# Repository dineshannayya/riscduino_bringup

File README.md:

# mpw_bringup
Host all the MPW Bring-up related Enviornment

Update

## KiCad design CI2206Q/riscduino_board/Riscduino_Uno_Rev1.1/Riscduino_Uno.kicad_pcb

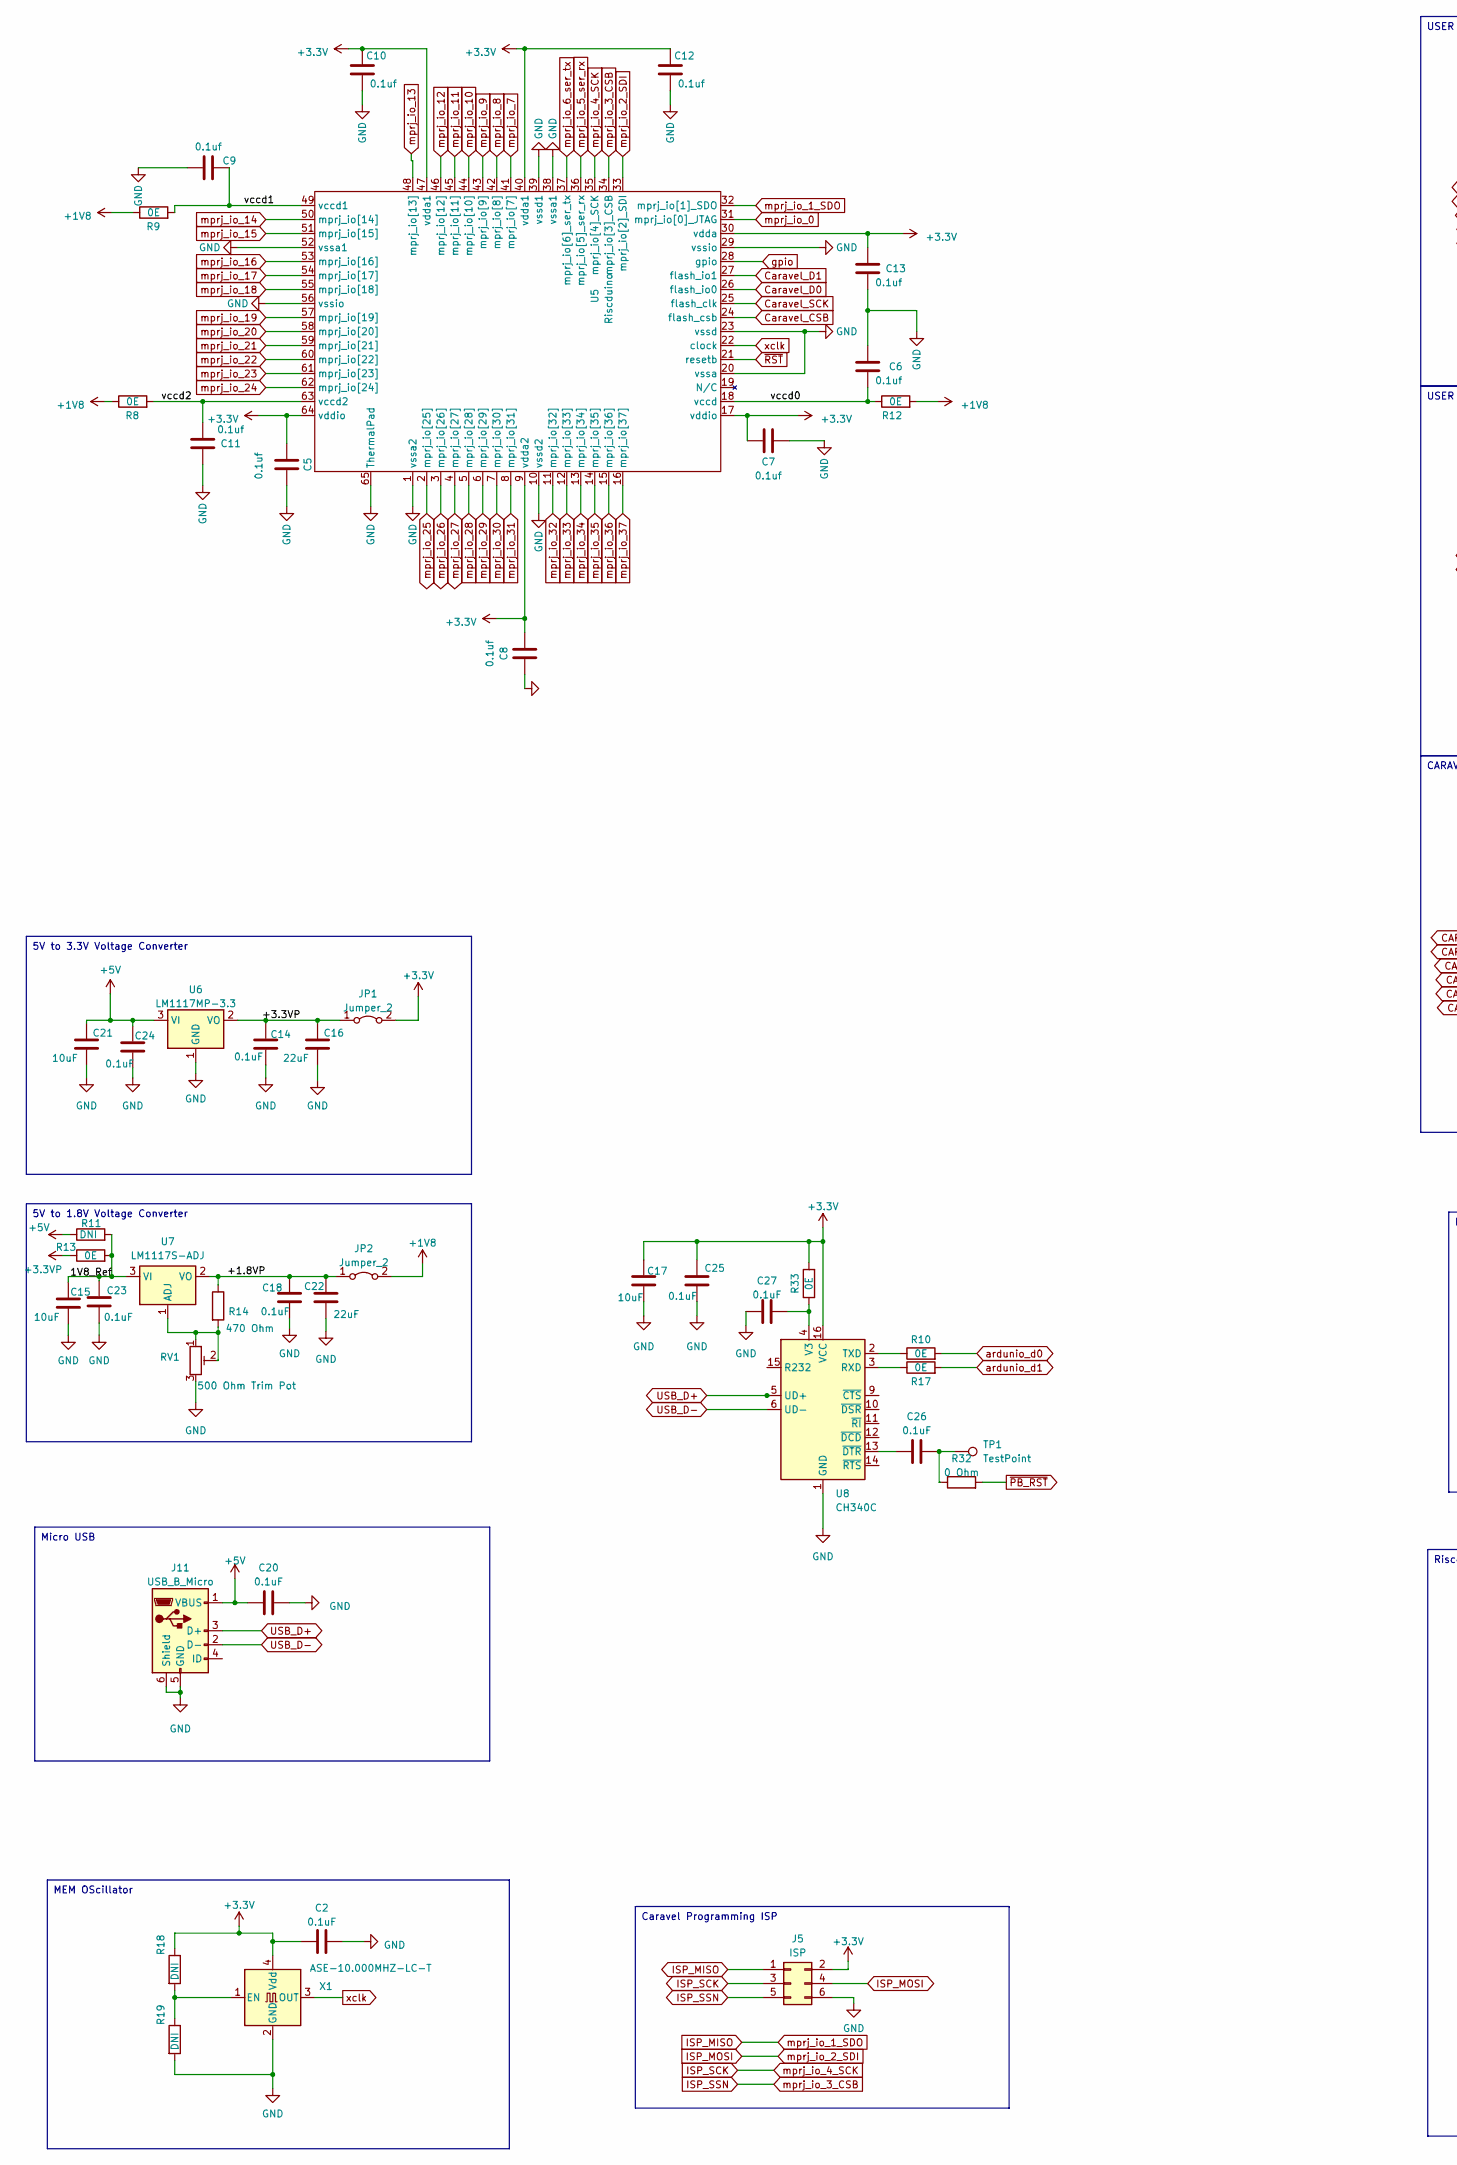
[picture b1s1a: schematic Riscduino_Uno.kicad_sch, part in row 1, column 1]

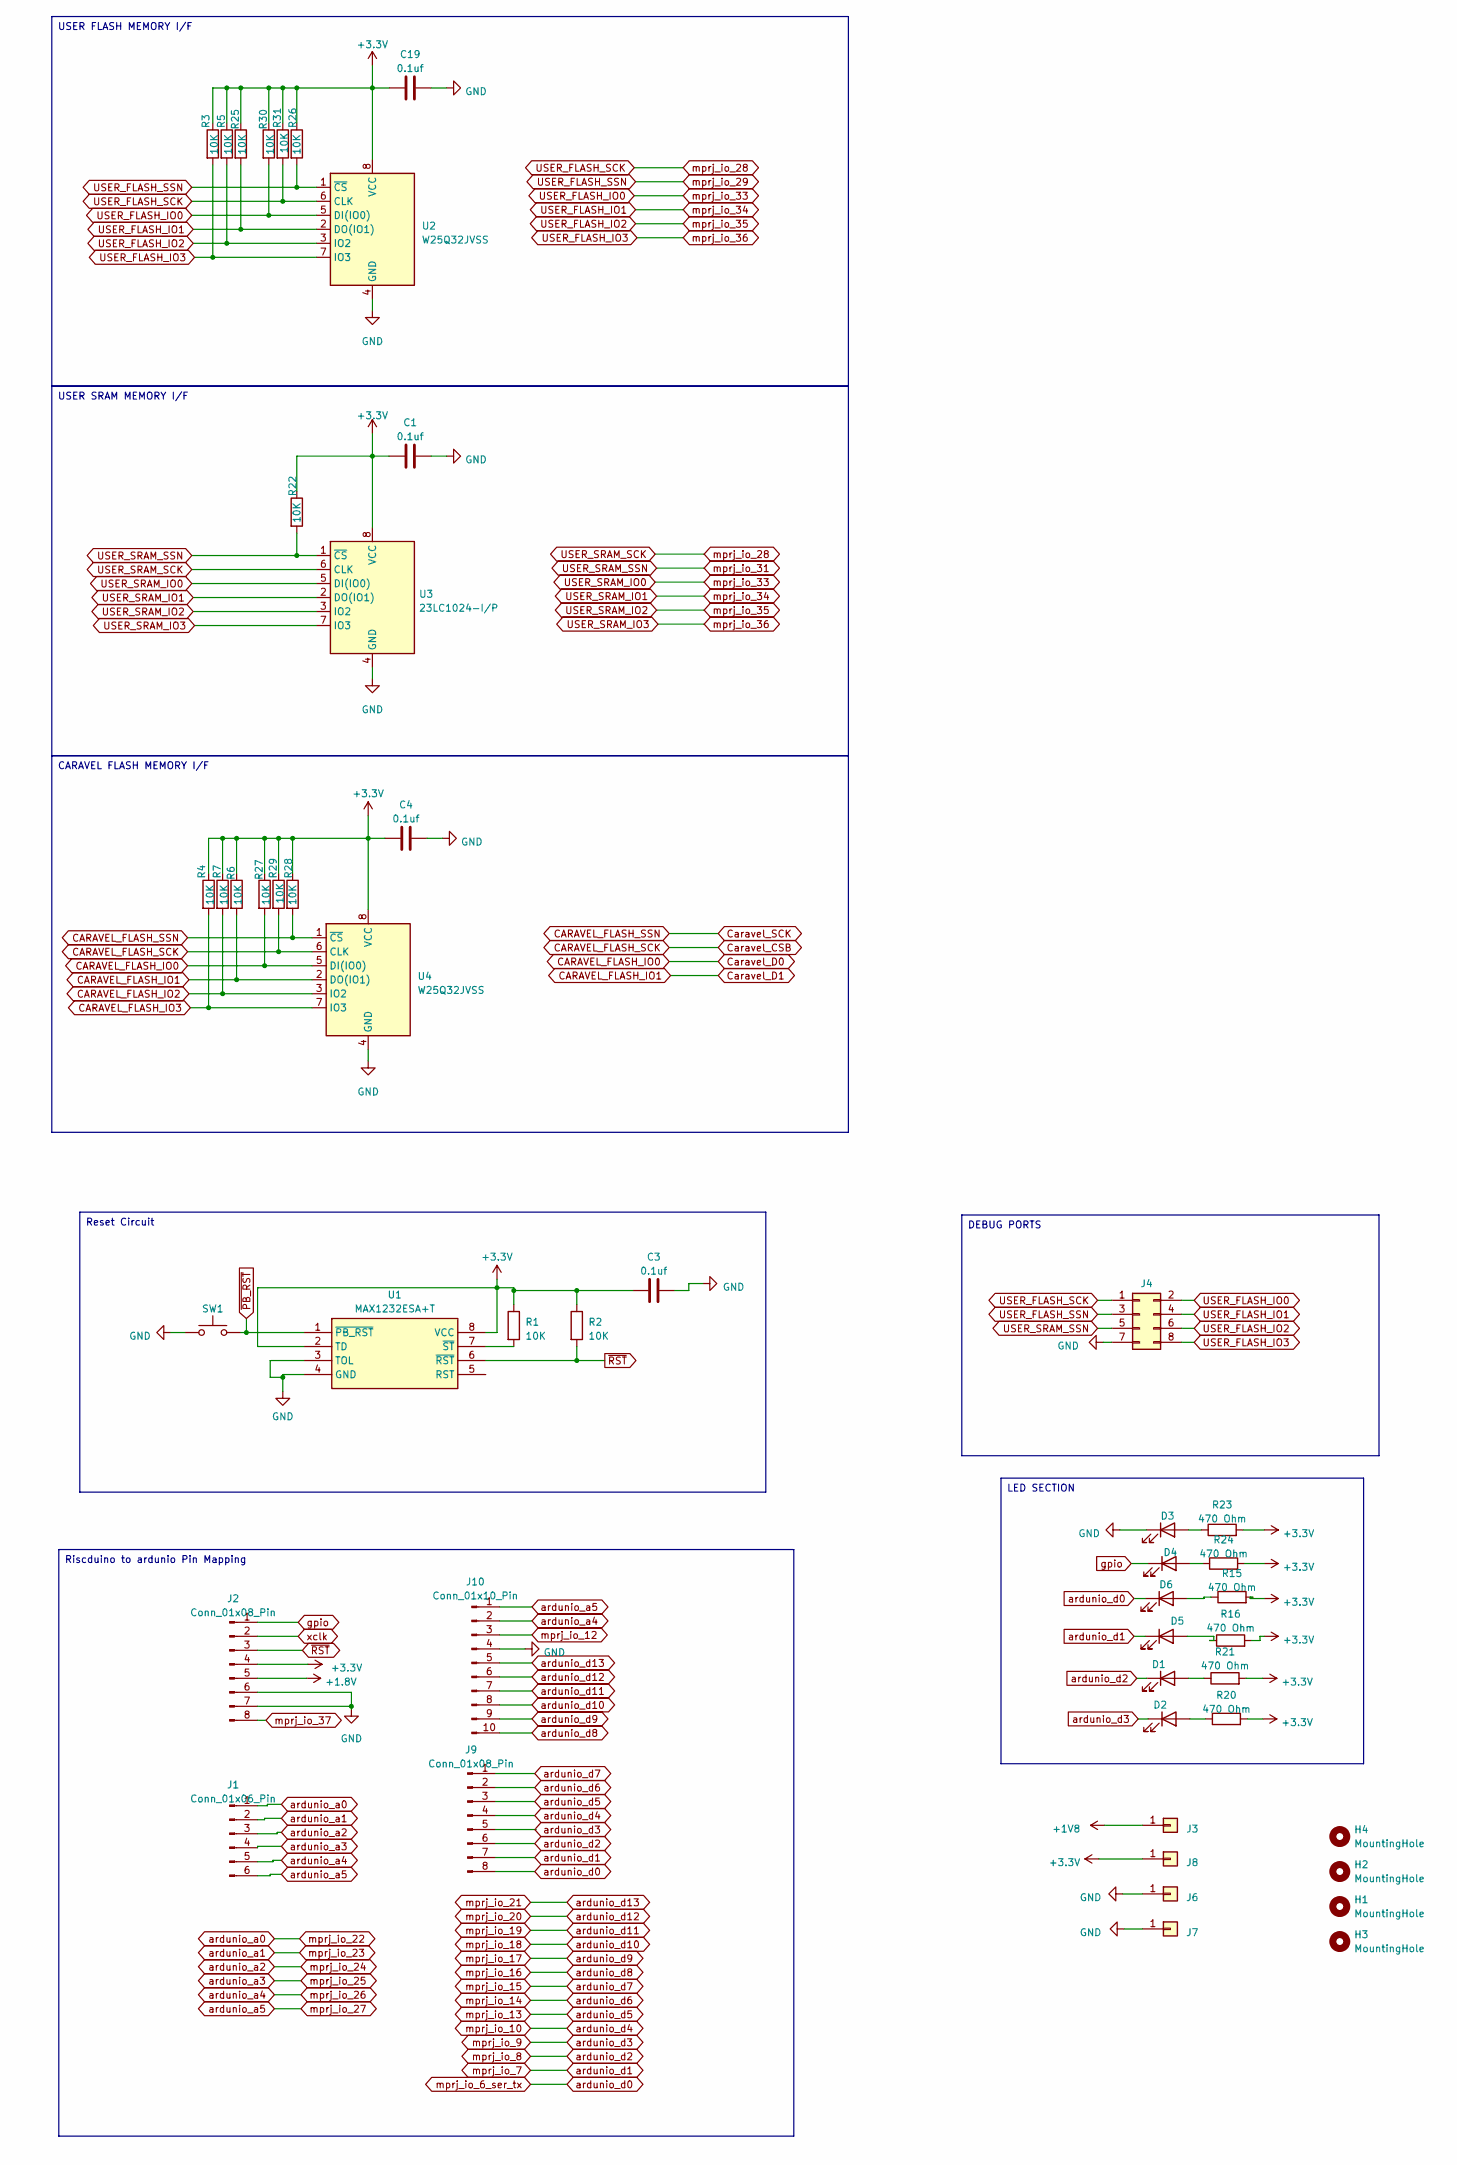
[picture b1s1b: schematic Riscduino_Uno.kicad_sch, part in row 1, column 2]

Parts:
C1, C3, C4, C5, C6, C7, C8, C9, C10, C11, C12, C13, C19: 0.1uf; C_0603_1608Metric_Pad1.08x0.95mm_HandSolder
C2, C14, C18, C20, C23, C24, C25, C26, C27: 0.1uF; C_0603_1608Metric_Pad1.08x0.95mm_HandSolder
C15, C17, C21: 10uF; C_0805_2012Metric_Pad1.18x1.45mm_HandSolder
C16, C22: 22uF; C_0805_2012Metric_Pad1.18x1.45mm_HandSolder
D1, D2, D4, D5: GREEN LED; LED_0805_2012Metric_Pad1.15x1.40mm_HandSolder
D3: RED LED; LED_0805_2012Metric_Pad1.15x1.40mm_HandSolder
D6: BLUE LED; LED_0805_2012Metric_Pad1.15x1.40mm_HandSolder
H1, H2, H3, H4: MountingHole; MountingHole_3.2mm_M3
J1: Conn_01x06_Pin; PinHeader_1x06_P2.54mm_Vertical
J2, J9: Conn_01x08_Pin; PinHeader_1x08_P2.54mm_Vertical
J3, J6, J7, J8: Conn_01x01; PinHeader_1x01_P2.54mm_Vertical
J4: Conn_02x04_Odd_Even; PinHeader_2x04_P2.54mm_Vertical
J5: ISP; PinHeader_2x03_P2.54mm_Vertical
J10: Conn_01x10_Pin; PinHeader_1x10_P2.54mm_Vertical
J11: USB_B_Micro; USB_Micro-B_Molex-105017-0001
JP1, JP2: Jumper_2; PinHeader_1x02_P2.54mm_Vertical
R1, R2, R3, R4, R5, R6, R7, R22, R25, R26, R27, R28, R29, R30, R31: 10K; R_0603_1608Metric_Pad0.98x0.95mm_HandSolder
R8, R9, R10, R12, R13, R17, R33: 0E; R_0603_1608Metric_Pad0.98x0.95mm_HandSolder
R11, R18, R19: DNI; R_0603_1608Metric_Pad0.98x0.95mm_HandSolder
R14, R15, R16, R20, R21, R23, R24: 470 Ohm; R_0603_1608Metric_Pad0.98x0.95mm_HandSolder
R32: 0 Ohm; R_0603_1608Metric_Pad0.98x0.95mm_HandSolder
RV1: 500 Ohm Trim Pot; Potentiometer_Bourns_3296W_Vertical
SW1: 4Pin Round Button SPST Straight Tactile Switch SM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; SW_SPST_EVPBF_TS4550TP
TP1: TestPoint; PinHeader_1x01_P2.54mm_Vertical
U1: MAX1232ESA+T; SOIC-8-1EP_3.9x4.9mm_P1.27mm_EP2.29x3mm; Manufacturer_Part_Number MAX1232ESA+T; Mouser Part Number 700-MAX1232ESAT
U2, U4: W25Q32JVSS; SOIC-8_5.23x5.23mm_P1.27mm
U3: 23LC1024-I/P; DIP-8_W7.62mm_LongPads
U5: Riscduino; RISCDUINO_QFN-64-1EP_9x9mm_P0.5mm_EP7.65x7.65mm_Ver1.1
U6: LM1117MP-3.3; SOT-223-3_TabPin2
U7: LM1117S-ADJ; SOT-223-3_TabPin2
U8: CH340C; SOIC-16_3.9x9.9mm_P1.27mm
X1: ASE-10.000MHZ-LC-T; Crystal_SMD_Abracon_ABM8G-4Pin_3.2x2.5mm

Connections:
+3.3V: C1.1, C2.1, C3.1, C4.1, C5.2, C7.2, C8.2, C10.1, C12.1, C13.1, C17.1, C19.1, C25.1, J2.4, J5.2, J8.1, JP1.2 (B), R1.1, R2.1, R3.1, R4.1, R5.1, R6.1, R7.1, R15.2, R16.2, R18.1, R20.2, R21.2, R22.1, R23.2, R24.2, R25.1, R26.1, R27.1, R28.1, R29.1, R30.1, R31.1, R33.2, U1.2 (TD), U1.8 (VCC), U2.8 (VCC), U3.8 (VCC), U4.8 (VCC), U5.9 (vdda2), U5.17 (vddio), U5.30 (vdda), U5.40 (vdda1), U5.47 (vdda1), U5.64 (vddio), U8.16 (VCC), X1.4 (Vdd)
+3.3VP: C14.1, C16.1, JP1.1 (A), R13.1, U6.2 (VO)
+5V: C20.1, C21.1, C24.1, J11.1 (VBUS), R11.1, U6.3 (VI)
/+1.8VP: C18.1, C22.1, JP2.1 (A), R14.1, U7.2 (VO)
/vccd0: C6.2, R12.1, U5.18 (vccd)
/vccd1: C9.2, R9.2, U5.49 (vccd1)
/vccd2: C11.1, R8.2, U5.63 (vccd2)
CARAVEL_FLASH_IO0: R27.2, U4.5 (DI(IO0)), U5.26 (flash_io0)
CARAVEL_FLASH_IO1: R6.2, U4.2 (DO(IO1)), U5.27 (flash_io1)
CARAVEL_FLASH_IO2: R7.2, U4.3 (IO2)
CARAVEL_FLASH_IO3: R4.2, U4.7 (IO3)
CARAVEL_FLASH_SCK: R29.2, U4.6 (CLK), U5.24 (flash_csb)
CARAVEL_FLASH_SSN: R28.2, U4.1 (~CS), U5.25 (flash_clk)
GND: C1.2, C2.2, C3.2, C4.2, C5.1, C6.1, C7.1, C8.1, C9.1, C10.2, C11.2, C12.2, C13.2, C14.2, C15.2, C16.2, C17.2, C18.2, C19.2, C20.2, C21.2, C22.2, C23.2, C24.2, C25.2, C27.1, D3.1 (K), J2.6, J2.7, J4.7, J5.6, J6.1, J7.1, J10.4, J11.5 (GND), J11.6 (Shield), R19.2, RV1.3, SW1.1, U1.3 (TOL), U1.4 (GND), U2.4 (GND), U3.4 (GND), U4.4 (GND), U5.1 (vssa2), U5.10 (vssd2), U5.20 (vssa), U5.23 (vssd), U5.29 (vssio), U5.38 (vssa1), U5.39 (vssd1), U5.52 (vssa1), U5.56 (vssio), U5.65 (ThermalPad), U6.1 (GND), U8.1 (GND), X1.2 (GND)
ISP_MISO: J5.1, U5.32 (mprj_io[1]_SDO)
ISP_MOSI: J5.4, U5.33 (mprj_io[2]_SDI)
ISP_SCK: J5.3, U5.35 (mprj_io[4]_SCK)
ISP_SSN: J5.5, U5.34 (mprj_io[3]_CSB)
unnamed: C26.2, R32.1, TP1.1
unnamed: D1.2 (A), R21.1
unnamed 20: D2.2 (A), R20.1; also elsewhere on the board
unnamed: D3.2 (A), R23.1
unnamed: D4.2 (A), R24.1
unnamed: D5.2 (A), R16.1
unnamed: D6.2 (A), R15.1
unnamed: R1.2, U1.7 (~ST)
unnamed: R14.2, RV1.1, RV1.2, U7.1 (ADJ)
unnamed: C15.1, C23.1, R11.2, R13.2, U7.3 (VI)
unnamed: R17.1, U8.3 (RXD)
unnamed: R10.1, U8.2 (TXD)
unnamed: C27.2, R33.1, U8.4 (V3)
unnamed: C26.1, U8.13 (~DTR)
unnamed: R18.2, R19.1, X1.1 (EN)
USB_D+: J11.3 (D+), U8.5 (UD+)
USB_D-: J11.2 (D-), U8.6 (UD-)
USER_FLASH_IO0: J4.2, R30.2, U2.5 (DI(IO0)), U3.5 (DI(IO0)), U5.12 (mprj_io[33])
USER_FLASH_IO1: J4.4, R25.2, U2.2 (DO(IO1)), U3.2 (DO(IO1)), U5.13 (mprj_io[34])
USER_FLASH_IO2: J4.6, R5.2, U2.3 (IO2), U3.3 (IO2), U5.14 (mprj_io[35])
USER_FLASH_IO3: J4.8, R3.2, U2.7 (IO3), U3.7 (IO3), U5.15 (mprj_io[36])
USER_FLASH_SCK: J4.1, R31.2, U2.6 (CLK), U3.6 (CLK), U5.5 (mprj_io[28])
USER_FLASH_SSN: J4.3, R26.2, U2.1 (~CS), U5.6 (mprj_io[29])
USER_SRAM_SSN: J4.5, R22.2, U3.1 (~CS), U5.8 (mprj_io[31])
ardunio_a0: J1.1, U5.60 (mprj_io[22])
ardunio_a1: J1.2, U5.61 (mprj_io[23])
ardunio_a2: J1.3, U5.62 (mprj_io[24])
ardunio_a3: J1.4, U5.2 (mprj_io[25])
ardunio_a4: J1.5, J10.2, U5.3 (mprj_io[26])
ardunio_a5: J1.6, J10.1, U5.4 (mprj_io[27])
ardunio_d0: D6.1 (K), J9.8, R10.2, U5.37 (mprj_io[6]_ser_tx)
ardunio_d1: D5.1 (K), J9.7, R17.2, U5.41 (mprj_io[7])
ardunio_d2: D1.1 (K), J9.6, U5.42 (mprj_io[8])
ardunio_d3: D2.1 (K), J9.5, U5.43 (mprj_io[9]); also elsewhere on the board
ardunio_d4: J9.4, U5.44 (mprj_io[10])
ardunio_d5: J9.3, U5.48 (mprj_io[13])
ardunio_d6: J9.2, U5.50 (mprj_io[14])
ardunio_d7: J9.1, U5.51 (mprj_io[15])
ardunio_d8: J10.10, U5.53 (mprj_io[16])
ardunio_d9: J10.9, U5.54 (mprj_io[17])
ardunio_d10: J10.8, U5.55 (mprj_io[18])
ardunio_d11: J10.7, U5.57 (mprj_io[19])
ardunio_d12: J10.6, U5.58 (mprj_io[20])
ardunio_d13: J10.5, U5.59 (mprj_io[21])
gpio: D4.1 (K), J2.1, U5.28 (gpio)
mprj_io_0: U5.31 (mprj_io[0]_JTAG)
mprj_io_5_ser_rx: U5.36 (mprj_io[5]_ser_rx)
mprj_io_11: U5.45 (mprj_io[11])
mprj_io_12: J10.3, U5.46 (mprj_io[12])
mprj_io_30: U5.7 (mprj_io[30])
mprj_io_32: U5.11 (mprj_io[32])
mprj_io_37: J2.8, U5.16 (mprj_io[37])
xclk: J2.2, U5.22 (clock), X1.3 (OUT)
~PB_RST: R32.2, SW1.2, U1.1 (~PB_RST)
~RST: J2.3, R2.2, U1.6 (~RST), U5.21 (resetb)

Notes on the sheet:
MEM OScillator
5V to 3.3V Voltage Converter
LED SECTION
Riscduino to ardunio Pin Mapping
Micro USB
USER SRAM MEMORY I/F
DEBUG PORTS
Caravel Programming ISP
USER FLASH MEMORY I/F
5V to 1.8V Voltage Converter
Reset Circuit
CARAVEL FLASH MEMORY I/F

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
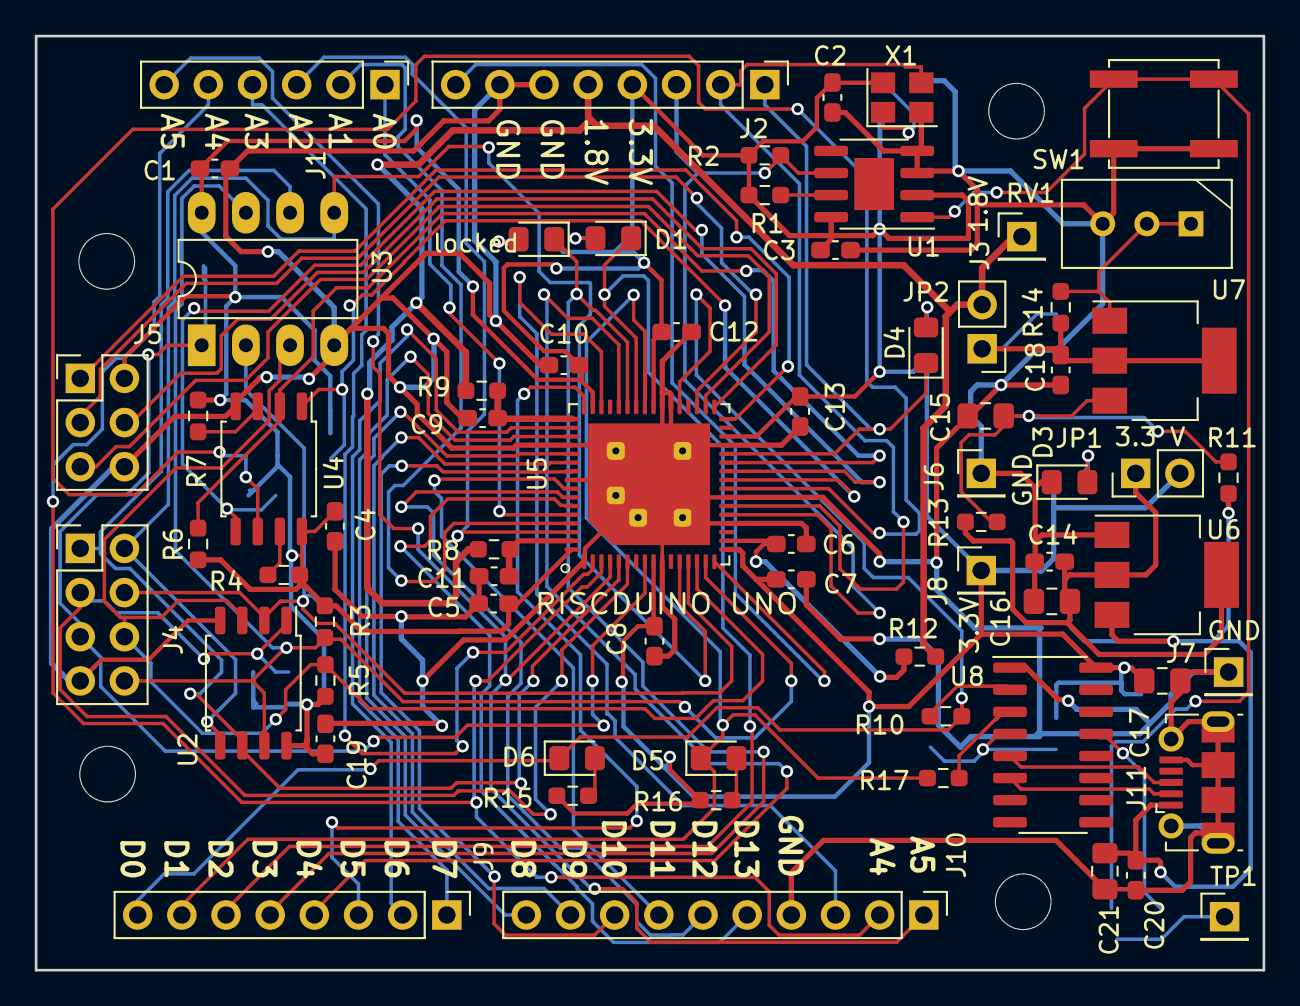
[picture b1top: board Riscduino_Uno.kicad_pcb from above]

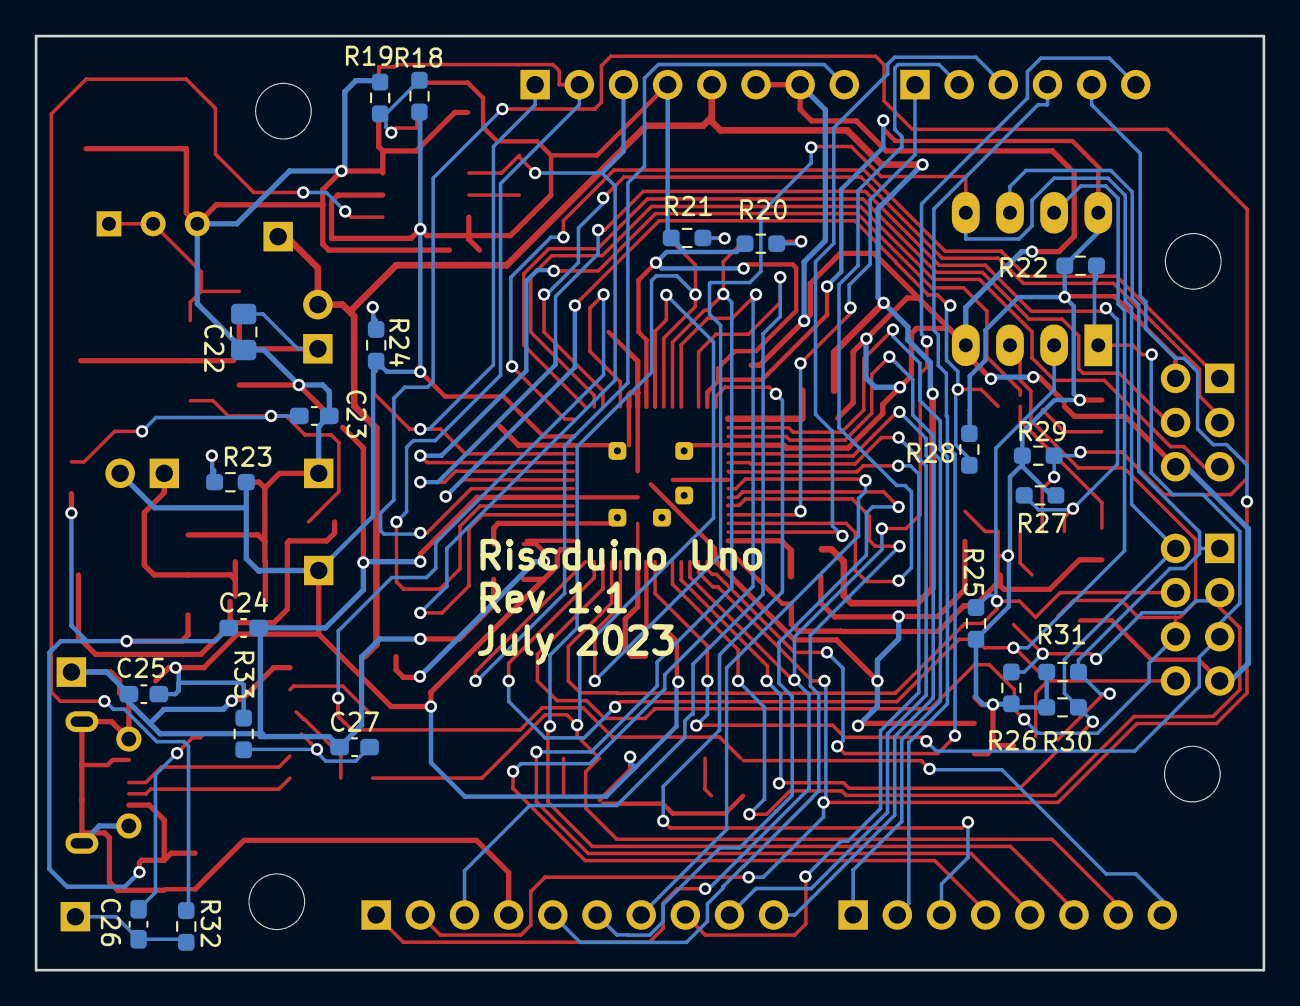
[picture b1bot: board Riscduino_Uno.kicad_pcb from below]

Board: 2 copper layers, 70.6 x 53.7 mm, 95 parts (22 on the bottom side), 69 nets.

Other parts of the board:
locked: GREEN LED; LED_0805_2012Metric_Pad1.15x1.40mm_HandSolder

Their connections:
unnamed 20: locked.2 (A); also elsewhere on the board
ardunio_d3: locked.1 (K); also elsewhere on the board

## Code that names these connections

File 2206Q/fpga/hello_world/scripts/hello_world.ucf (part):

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
### Strap Mapping
#parameter PSTRAP_DEFAULT_VALUE = 15'b000_0110_1010_0000;
#   Pin-11        5             PD5/WS[2]/SS[3]/OC0B(PWM1)/T1   strap[0] -0  digital_io[13]
#   Pin-12        6             PD6/WS[2]/SS[2]/OC0A(PWM2)/AIN0 strap[1] -0  digital_io[14]/analog_io[2]
#   Pin-13        7             PD7/WS[2]/A1N1                  strap[2] -0  digital_io[15]/analog_io[3]
#   Pin-14        8             PB0/WS[2]/CLKO/ICP1             strap[3] -0  digital_io[16]
#   Pin-15        9             PB1/WS[3]/SS[1]OC1A(PWM3)       strap[4] -0  digital_io[17]
#   Pin-16        10            PB2/WS[3]/SS[0]/OC1B(PWM4)      strap[5] -1  digital_io[18]
#   Pin-17        11            PB3/WS[3]/MOSI/OC2A(PWM5)       strap[6] -0  digital_io[19]
#   Pin-18        12            PB4/WS[3]/MISO                  strap[7] -1  digital_io[20]
#                               sflash_ss[0]                    strap[8] -0  digital_io[29]
#                               sflash_ss[1]                    strap[9] -1  digital_io[30]
#                               sflash_ss[2]                    strap[10]-1  digital_io[31]
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###################################################################################################################################################
#                                                   HEADER P1                                                                                     #
###################################################################################################################################################
###NET "IO_P1[3]"   LOC = P35  | IOSTANDARD = LVCMOS33 | DRIVE = 8 | SLEW = FAST ;                # IO_L1P_3           	        Sch = GPIO-P18 
###NET "IO_P1[4]"   LOC = P34  | IOSTANDARD = LVCMOS33 | DRIVE = 8 | SLEW = FAST ;                # IO_L1N_VREF_3      		Sch = GPIO-N18 
NET "mprj_io[0]" LOC = P33 | IOSTANDARD = "LVCMOS33" | DRIVE = 8 | SLEW = FAST;               # IO_L2P_3	   		Sch = GPIO-P17 
NET "mprj_io[1]" LOC = P32 | IOSTANDARD = "LVCMOS33" | DRIVE = 8 | SLEW = FAST;               # IO_L2N_3           		Sch = GPIO-N17 
NET "mprj_io[2]" LOC = P30 | IOSTANDARD = "LVCMOS33" | DRIVE = 8 | SLEW = FAST;               # IO_L36P_3          	        Sch = GPIO-P16 
NET "mprj_io[3]" LOC = P29 | IOSTANDARD = "LVCMOS33" | DRIVE = 8 | SLEW = FAST;               # IO_L36N_3          		Sch = GPIO-N16 
NET "mprj_io[4]" LOC = P27 | IOSTANDARD = "LVCMOS33" | DRIVE = 8 | SLEW = FAST;               # IO_L37P_3	   		Sch = GPIO-P15 
NET "mprj_io[5]" LOC = P26 | IOSTANDARD = "LVCMOS33" | DRIVE = 8 | SLEW = FAST;               # IO_L37N_3          		Sch = GPIO-N15 
NET "mprj_io[6]" LOC = P24 | IOSTANDARD = "LVCMOS33" | DRIVE = 8 | SLEW = FAST;               # IO_L41P_GCLK27_3   	        Sch = GPIO-P14 
NET "mprj_io[7]" LOC = P23 | IOSTANDARD = "LVCMOS33" | DRIVE = 8 | SLEW = FAST;               # IO_L41N_GCLK26_3   		Sch = GPIO-N14 
##NET "IO_P1[13]"   LOC = P22  | IOSTANDARD = LVCMOS33 | DRIVE = 8 | SLEW = FAST ;                # IO_L42P_GCLK25_TRDY2_3      Sch = GPIO-P13 
#As flash_spi  sclk port need to fpga clock buf port we are connecting IO_P2[28] to mprj_io[28], you need to add wire connection at board
NET "mprj_io[28]" LOC = P21 | IOSTANDARD = "LVCMOS33" | DRIVE = 8 | SLEW = FAST;                # IO_L42N_GCLK24_3   		Sch = GPIO-N13 
##NET "IO_P1[14]"   LOC = P21  | IOSTANDARD = LVCMOS33 | DRIVE = 8 | SLEW = FAST ;                # IO_L42N_GCLK24_3   		Sch = GPIO-N13 
NET "mprj_io[8]" LOC = P17 | IOSTANDARD = "LVCMOS33" | DRIVE = 8 | SLEW = FAST;               # IO_L43P_GCLK23_3   	        Sch = GPIO-P12 
NET "mprj_io[9]" LOC = P16 | IOSTANDARD = "LVCMOS33" | DRIVE = 8 | SLEW = FAST;               # IO_L43N_GCLK22_IRDY2_3      Sch = GPIO-N12
NET "mprj_io[10]" LOC = P15 | IOSTANDARD = "LVCMOS33" | DRIVE = 8 | SLEW = FAST;               # IO_L44P_GCLK21_3   	        Sch = GPIO-P11
NET "mprj_io[11]" LOC = P14 | IOSTANDARD = "LVCMOS33" | DRIVE = 8 | SLEW = FAST;               # IO_L44N_GCLK20_3   		Sch = GPIO-N11
NET "mprj_io[12]" LOC = P12 | IOSTANDARD = "LVCMOS33" | DRIVE = 8 | SLEW = FAST;               # IO_L49P_3          	        Sch = GPIO-P10
NET "mprj_io[13]" LOC = P11 | IOSTANDARD = "LVCMOS33" | DRIVE = 8 | SLEW = FAST | PULLDOWN;    # IO_L49N_3          		Sch = GPIO-N10 
NET "mprj_io[14]" LOC = P10 | IOSTANDARD = "LVCMOS33" | DRIVE = 8 | SLEW = FAST | PULLDOWN;    # IO_L50P_3 	   		Sch = GPIO-P9 
NET "mprj_io[15]" LOC = P9 | IOSTANDARD = "LVCMOS33" | DRIVE = 8 | SLEW = FAST | PULLDOWN;   # IO_L50N_3           	Sch = GPIO-N9
##NET "IO_P1[23]"   LOC = P8   | IOSTANDARD = LVCMOS33 | DRIVE = 8 | SLEW = FAST ;                # IO_L51P_3	   		Sch = GPIO-P8 
##NET "IO_P1[24]"   LOC = P7   | IOSTANDARD = LVCMOS33 | DRIVE = 8 | SLEW = FAST ;                # IO_L51N_3           	Sch = GPIO-N8
NET "mprj_io[16]" LOC = P6 | IOSTANDARD = "LVCMOS33" | DRIVE = 8 | SLEW = FAST | PULLDOWN;    # IO_L52P_3	   		Sch = GPIO-P7 
NET "mprj_io[17]" LOC = P5 | IOSTANDARD = "LVCMOS33" | DRIVE = 8 | SLEW = FAST | PULLDOWN;    # IO_L52N_3          		Sch = GPIO-N7
NET "mprj_io[18]" LOC = P2 | IOSTANDARD = "LVCMOS33" | DRIVE = 8 | SLEW = FAST | PULLUP;      # IO_L83P_3	  		Sch = GPIO-P6
#NET "rstn"         LOC = P1   | IOSTANDARD = LVCMOS33 | DRIVE = 8 | SLEW = FAST ;                # IO_L83N_VREF_3     	        Sch = GPIO-N6
NET "mrn" LOC = P142 | IOSTANDARD = "LVCMOS33" | DRIVE = 8 | SLEW = FAST;               # IO_L2P_0	   		Sch = GPIO-P5
###NET "i2c_scl"    LOC = P141 | IOSTANDARD = LVCMOS33 | DRIVE = 8 | SLEW = FAST ;                # IO_L2N_0           		Sch = GPIO-N5
##NET "i2c_sda"     LOC = P140 | IOSTANDARD = LVCMOS33 | DRIVE = 8 | SLEW = FAST ;                # IO_L3P_0	   		Sch = GPIO-P4
##NET "trigger"       LOC = P140 | IOSTANDARD = "LVCMOS33" | DRIVE = 8 | SLEW = FAST;               # IO_L3P_0	   		Sch = GPIO-P4
##NET "gpio"        LOC = P139 | IOSTANDARD = LVCMOS33 | DRIVE = 8 | SLEW = FAST ;                # IO_L3N_0 	   		Sch = GPIO-N4
###NET "IO_P1[33]"  LOC = P138 | IOSTANDARD = LVCMOS33 | DRIVE = 8 | SLEW = FAST ;                # IO_L4P_0	   		Sch = GPIO-P3
###NET "IO_P1[34]"  LOC = P137 | IOSTANDARD = LVCMOS33 | DRIVE = 8 | SLEW = FAST ;                # IO_L4N_0   	   		Sch = GPIO-N3
NET "tim3_ch2" LOC = P134 | IOSTANDARD = "LVCMOS33" | DRIVE = 8 | SLEW = FAST;               # IO_L34P_GCLK19_0  	        Sch = GPIO-P2
##NET "xclk"        LOC = P133 | IOSTANDARD = LVCMOS33 | DRIVE = 8 | SLEW = FAST ;                # IO_L34N_GCLK18_0   		Sch = GPIO-N2
###NET "IO_P1[37]"  LOC = P132 | IOSTANDARD = LVCMOS33 | DRIVE = 8 | SLEW = FAST ;                # IO_L35P_GCLK17_0   	        Sch = GPIO-P1
##NET "IO_P1[38]"   LOC = P131 | IOSTANDARD = LVCMOS33 | DRIVE = 8 | SLEW = FAST ;                # IO_L35N_GCLK16_0    	Sch = GPIO-N1
####################################################################################################################################################
##                                                   HEADER P2                                                                                     #
####################################################################################################################################################
NET "mprj_io[19]" LOC = P43 | IOSTANDARD = "LVCMOS33" | DRIVE = 8 | SLEW = FAST | PULLDOWN;    # IO_L62N_D6_2                  Sch = GPIO-N23 
NET "mprj_io[20]" LOC = P44 | IOSTANDARD = "LVCMOS33" | DRIVE = 8 | SLEW = FAST | PULLUP;      # IO_L62P_D5_2	                Sch = GPIO-P23 
NET "mprj_io[21]" LOC = P45 | IOSTANDARD = "LVCMOS33" | DRIVE = 8 | SLEW = FAST;              # IO_L49N_D4_2	                Sch = GPIO-N25 
NET "mprj_io[22]" LOC = P46 | IOSTANDARD = "LVCMOS33" | DRIVE = 8 | SLEW = FAST;              # IO_L49P_D3_2	                Sch = GPIO-P25 
NET "mprj_io[23]" LOC = P47 | IOSTANDARD = "LVCMOS33" | DRIVE = 8 | SLEW = FAST;              # IO_L48N_RDWR_B_VREF_2         Sch = GPIO-N24 
NET "mprj_io[24]" LOC = P48 | IOSTANDARD = "LVCMOS33" | DRIVE = 8 | SLEW = FAST;              # IO_L48P_D7_2			Sch = GPIO-P24 
NET "mprj_io[25]" LOC = P50 | IOSTANDARD = "LVCMOS33" | DRIVE = 8 | SLEW = FAST;              # IO_L31N_GCLK30_D15_2	  	Sch = GPIO-N22 
NET "mprj_io[26]" LOC = P51 | IOSTANDARD = "LVCMOS33" | DRIVE = 8 | SLEW = FAST;              # IO_L31P_GCLK31_D14_2      	Sch = GPIO-P22 
NET "mprj_io[29]" LOC = P55 | IOSTANDARD = "LVCMOS33" | DRIVE = 8 | SLEW = FAST | PULLDOWN;              # IO_L30N_GCLK0_USERCCLK_2  	Sch = GPIO-N19 
NET "mprj_io[30]" LOC = P56 | IOSTANDARD = "LVCMOS33" | DRIVE = 8 | SLEW = FAST | PULLUP;               # IO_L30P_GCLK1_D13_2	  	Sch = GPIO-P19 
#NET "IO_P2[13]"   LOC = P74   | IOSTANDARD = LVCMOS33 | DRIVE = 8 | SLEW = FAST ;              # IO_L74N_DOUT_BUSY_1       	Sch = GPIO-N26 
#NET "IO_P2[14]"   LOC = P75   | IOSTANDARD = LVCMOS33 | DRIVE = 8 | SLEW = FAST ;              # IO_L74P_AWAKE_1		Sch = GPIO-P26
NET "mprj_io[27]" LOC = P78 | IOSTANDARD = "LVCMOS33" | DRIVE = 8 | SLEW = FAST;              # IO_L47N_1	   		Sch = GPIO-N27
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
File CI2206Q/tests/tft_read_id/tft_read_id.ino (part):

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#define LCD_D7 7

   //LCD pins  |D7 |D6 |D5 |D4 |D3 |D2 |D1 |D0 | |RD |WR |RS |CS |RST|
   //AVR   pin |PD7|PD6|PD5|PD4|PD3|PD2|PB1|PB0| |PC0|PC1|PC2|PC3|PC4|
   //UNO pins  |7  |6  |5  |4  |3  |2  |9  |8  | |A0 |A1 |A2 |A3 |A4 |
   #define RD_PORT PORTC
   #define RD_PIN  0
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#define WriteCmd(x)  { CD_COMMAND; write16(x); CD_DATA; }
#define WriteData(x) { write16(x); }

#define reg_gpio_dsel         (*(volatile uint32_t*)0x10020080)  // reg_0  - GPIO Direction Select
#define reg_gpio_type         (*(volatile uint32_t*)0x10020084)  // reg_1  - GPIO TYPE - Static/Waveform
#define reg_gpio_idata        (*(volatile uint32_t*)0x10020088)  // reg_2  - GPIO Data In
#define reg_gpio_odata        (*(volatile uint32_t*)0x1002008C)  // reg_3  - GPIO Data Out
#define reg_gpio_intr_stat    (*(volatile uint32_t*)0x10020090)  // reg_4  - GPIO Interrupt status
#define reg_gpio_intr_clr     (*(volatile uint32_t*)0x10020090)  // reg_5  - GPIO Interrupt Clear
#define reg_gpio_intr_set     (*(volatile uint32_t*)0x10020094)  // reg_6 - GPIO Interrupt Set
#define reg_gpio_intr_mask    (*(volatile uint32_t*)0x10020098)  // reg_7 - GPIO Interrupt Mask
#define reg_gpio_pos_intr     (*(volatile uint32_t*)0x1002009C)  // reg_8 - GPIO Posedge Interrupt
#define reg_gpio_neg_intr     (*(volatile uint32_t*)0x100200A0)  // reg_9 - GPIO Neg Interrupt


void setup()
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void lcdInit()
{

    Serial.print("GPIO Direction(Pre):");
    Serial.println(reg_gpio_dsel) ;
    Serial.print("GPIO Type(Pre):");
    Serial.println(reg_gpio_type) ;
    Serial.print("GPIO Output(Pre):");
    Serial.println(reg_gpio_odata) ;
    
    
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    CTL_INIT();
    CTL_IDLE();

    Serial.print("GPIO Direction(Post):");
    Serial.println(reg_gpio_dsel) ;
    Serial.print("GPIO Type(Post):");
    Serial.println(reg_gpio_type) ;
    Serial.print("GPIO Output(Post):");
    Serial.println(reg_gpio_odata) ;
    
}
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
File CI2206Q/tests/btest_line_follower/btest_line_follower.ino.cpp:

#include <Arduino.h>
#line 1 "/home/dinesha/workarea/opencore/git/riscduino_bringup/2206Q/tests/btest_line_follower/btest_line_follower.ino"
/*************************************************************
  Connection Setting of RoboMart Line Follower Development Kit
  Reference: https://www.scribd.com/document/238827643/User-Manual-IBOT-Mini-V3#

LEDs  ---@----------------> PB1  - D9   -->  Output
LEDs  ---@----------------> PB2  - D10  -->  Output
LEDs  ---@----------------> PB3  - D11  -->  Output
LEDs  ---@----------------> PB4  - D12  -->  Output
Left Sensor  -------------> PC3 -  A3/D17   -->  Input
Right Sensor -------------> PC0 -  A0/D14   -->  Input
Buzzer       -------------> PD4 -  D4   ---> Output
Right Motor (+) ----------> PB1  - D9   ---> Output
Right Motor (-) ----------> PB2  - D10  ---> Output
Left Motor (-) ----------> PB3  - D11  ---> Output
Left Motor (+) ----------> PB4  - D12  ---> Output
Buzzer          ----------> PD4  - D4   ---> Output
RESET --------------------> PC6  - RESET
Crystall Oscialltor (12Mhz) --> PB6 and PB7
VB = Battery Supply
VCC = Regulated 5V+
Gnd = Gnd (0V)
*************************************************************/
#define RIGHT_MOTOR_P  9
#define RIGHT_MOTOR_N  10
#define LEFT_MOTOR_N   11
#define LEFT_MOTOR_P   12
#define LEFT_SENSOR    17
#define RIGHT_SENSOR   14
#define BUZZER         4

int BuzzerValue=0x00;

#line 33 "/home/dinesha/workarea/opencore/git/riscduino_bringup/2206Q/tests/btest_line_follower/btest_line_follower.ino"
void setup();
#line 50 "/home/dinesha/workarea/opencore/git/riscduino_bringup/2206Q/tests/btest_line_follower/btest_line_follower.ino"
void loop();
#line 33 "/home/dinesha/workarea/opencore/git/riscduino_bringup/2206Q/tests/btest_line_follower/btest_line_follower.ino"
  void setup() {
  // put your setup code here, to run once:
  // Motor
    pinMode(RIGHT_MOTOR_P, OUTPUT);
    pinMode(RIGHT_MOTOR_N, OUTPUT);
    pinMode(LEFT_MOTOR_N, OUTPUT);
    pinMode(LEFT_MOTOR_P, OUTPUT);

  // Buzer
    pinMode(BUZZER, OUTPUT);
    // Sensor
    pinMode(LEFT_SENSOR, INPUT);
    pinMode(RIGHT_SENSOR, INPUT);


}

void loop() {
  // put your main code here, to run repeatedly:
  int LeftSensorVal = digitalRead(LEFT_SENSOR);
  int RightSensorVal = digitalRead(RIGHT_SENSOR);

 // When both Sensor Off , Then Stop Motor
 if(LeftSensorVal ==0 && RightSensorVal == 0){
    digitalWrite(RIGHT_MOTOR_P, HIGH);
    digitalWrite(RIGHT_MOTOR_N, HIGH);
    digitalWrite(LEFT_MOTOR_N, HIGH);
    digitalWrite(LEFT_MOTOR_P, HIGH);
    BuzzerValue = LOW;

  }

      // Turn Right
 if(LeftSensorVal ==0 && RightSensorVal == 1){
    digitalWrite(RIGHT_MOTOR_P, LOW);
    digitalWrite(RIGHT_MOTOR_N, LOW);
    digitalWrite(LEFT_MOTOR_N, LOW);
    digitalWrite(LEFT_MOTOR_P, HIGH);
    BuzzerValue = HIGH;
 }

        // Turn Left
 if(LeftSensorVal ==1 && RightSensorVal == 0){
    digitalWrite(RIGHT_MOTOR_P, HIGH);
    digitalWrite(RIGHT_MOTOR_N, LOW);
    digitalWrite(LEFT_MOTOR_N, LOW);
    digitalWrite(LEFT_MOTOR_P, LOW);
    BuzzerValue = HIGH;
  }

  // Turn Move Forward
 if(LeftSensorVal ==1 && RightSensorVal == 1){
    digitalWrite(RIGHT_MOTOR_P, HIGH);
    digitalWrite(RIGHT_MOTOR_N, LOW);
    digitalWrite(LEFT_MOTOR_N, LOW);
    digitalWrite(LEFT_MOTOR_P, HIGH);
    BuzzerValue = ~BuzzerValue;
  }
  digitalWrite(BUZZER, BuzzerValue);

}

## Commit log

2023-01-11 initial version
2023-01-11 added led driver
2023-01-16 nucleo scripts
2023-01-17 caravel Schematics
2023-01-18 test bench
2023-01-18 Debug capture added
2023-01-19 logs
2023-01-25 script update
2023-01-26 yifive specific test case
2023-01-26 hex file added
2023-01-26 CLEANUP
2023-01-28 First MPW-2 Waveform at SPI
2023-01-28 first spi transaction capture
2023-01-28 report dir movement
2023-01-30 ftdi test added
2023-02-04 boot test update
2023-02-05 waveform update
2023-02-05 risc boot
2023-02-12 qspis added
2023-02-13 hello world xilnux project
2023-02-13 working set
2023-02-13 hex file
2023-02-13 hex update
2023-02-14 xilinx model/xilinx/BRAM_SINGLE_MACRO.v added
2023-02-15 LogicAnalyserCapture/LA-Capture-FPGA.sal
2023-02-17 drawing
2023-02-19 update with Risc Req 0x200 followed by 0x1C0
2023-02-19 readme added
2023-02-22 mpw-2 status
2023-02-27 Riscduino Board Ver0.2
2023-02-28 Schematics & PCB PDF files
2023-03-02 pcb update
2023-03-03 test case waveform
2023-03-11 waveform-fpga data response
2023-03-11 FPGA update
2023-03-11 Reset sync update
2023-03-11 user c code added
2023-03-11 RTL working waveform
2023-03-11 Bug fix
2023-06-20 2206Q file addition
2023-06-20 2206Q test case
2023-06-21 2206q fpga directory added'
2023-06-21 Update pinmapping as per 2206Q
2023-06-21 test case clean up for 2206Q
2023-06-21 hex init update
2023-06-23 riscv boot test added
2023-06-25 Board Images update
2023-06-27 hex address map fix
2023-06-27 temp removed BSS
2023-06-28 working riscv boot
2023-06-28 working hello world test
2023-06-28 btest0 added into git
2023-06-28 btest0 update
2023-06-29 doc update
2023-06-29 bringup test2
2023-07-03 PPT Added
2023-07-08 ftdi pinout
2023-07-08 flash data sheet
2023-07-08 user_flash => fpga
2023-07-08 fpga/hex user_flash
2023-07-08 working sram access
2023-07-12 first working arduino tests
2023-07-21 Riscduino Uno Reference Schematic
2023-07-21 1.0.3 Update
2023-07-21 1.0.4
2023-07-22 1.0.7 DRC Clean, Power Routed
2023-07-22 Gerber 1.0 Release to Lion Circuit
2023-07-22 1.0.9
2023-07-22 Riscduino Debug 1.0
2023-07-22 Images
2023-07-22 Schematic PDF files
2023-07-24 BOM Added
2023-07-25 Board Version 1.1
2023-07-25 riscduino board movement
2023-07-25 gerber
2023-07-27 TCM test case
2023-07-30 line follower
2023-07-30 Line Follower Update
2023-08-11 board removed from repo
2023-08-14 LineFollower Test
2023-08-17 SPI Debug Step Added
2023-08-18 caravel flash scripts updated for user qspi mode
2023-08-19 update + keypad caravel flash
2023-08-21 Custom KeyPad Scripts
2023-08-22 gpio outputs
2023-08-22 gpio output test
2023-08-28 test update
2023-08-31 TFT Sample Test
2023-08-31 tft read id
2023-09-01 line follower test
2023-09-02 user cache enabled
2023-09-14 PWM waveform
2023-09-14 pwm test
2023-09-14 working pwm
2023-12-20 CI2306Q Silicon Status
2023-12-20 CI2306Q Silicon Status update
2023-12-20 CI2306Q Status update
